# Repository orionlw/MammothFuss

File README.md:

Mammoth Fuzz
Fuzz pedal schematic using EagleCAD

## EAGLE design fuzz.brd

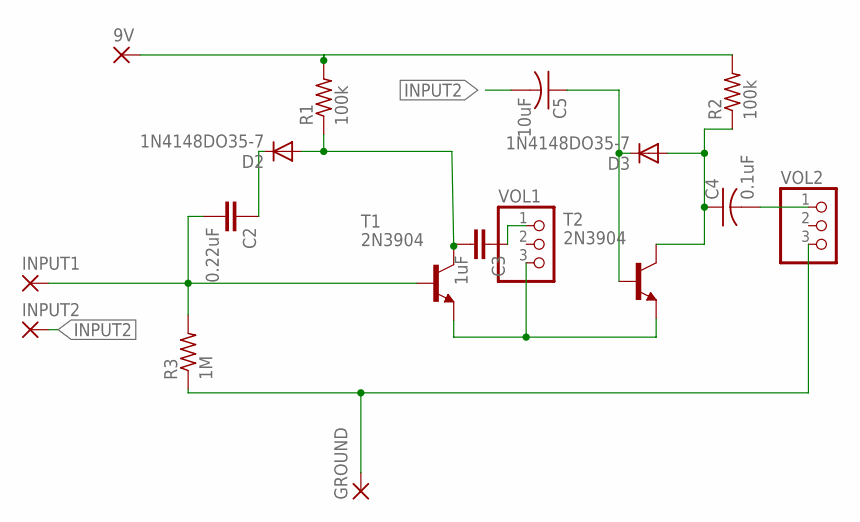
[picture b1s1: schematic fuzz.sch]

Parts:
9V: 2,15/1,0
C2: 0.22uF; C025-025X050
C3: 1uF; C025-025X050
C4: 0.1uF; C025-025X050
C5: 10uF; C025-025X050
D2, D3: 1N4148DO35-7; DO35-7
GROUND: 2,15/1,0
INPUT1, INPUT2: 2,15/1,0
R1, R2: 100k; 0207/10
R3: 1M; 0207/10
T1, T2: 2N3904; TO92
VOL1, VOL2: PINHD-1X3; 1X03

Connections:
INPUT2: C5.2, INPUT2.1
unnamed: C3.1, VOL1.1
unnamed: C2.2, INPUT1.1, R3.2, T1.2 (B)
unnamed: C3.2, D2.A, R1.1, T1.1 (C)
unnamed: C5.1, D3.C, T2.2 (B)
unnamed: C4.1, D3.A, R2.1, T2.1 (C)
unnamed: 9V.1, R1.2, R2.2
unnamed: C4.2, VOL2.1
unnamed: T1.3 (E), T2.3 (E), VOL1.3
unnamed: GROUND.1, R3.1, VOL2.3
unnamed: C2.1, D2.C

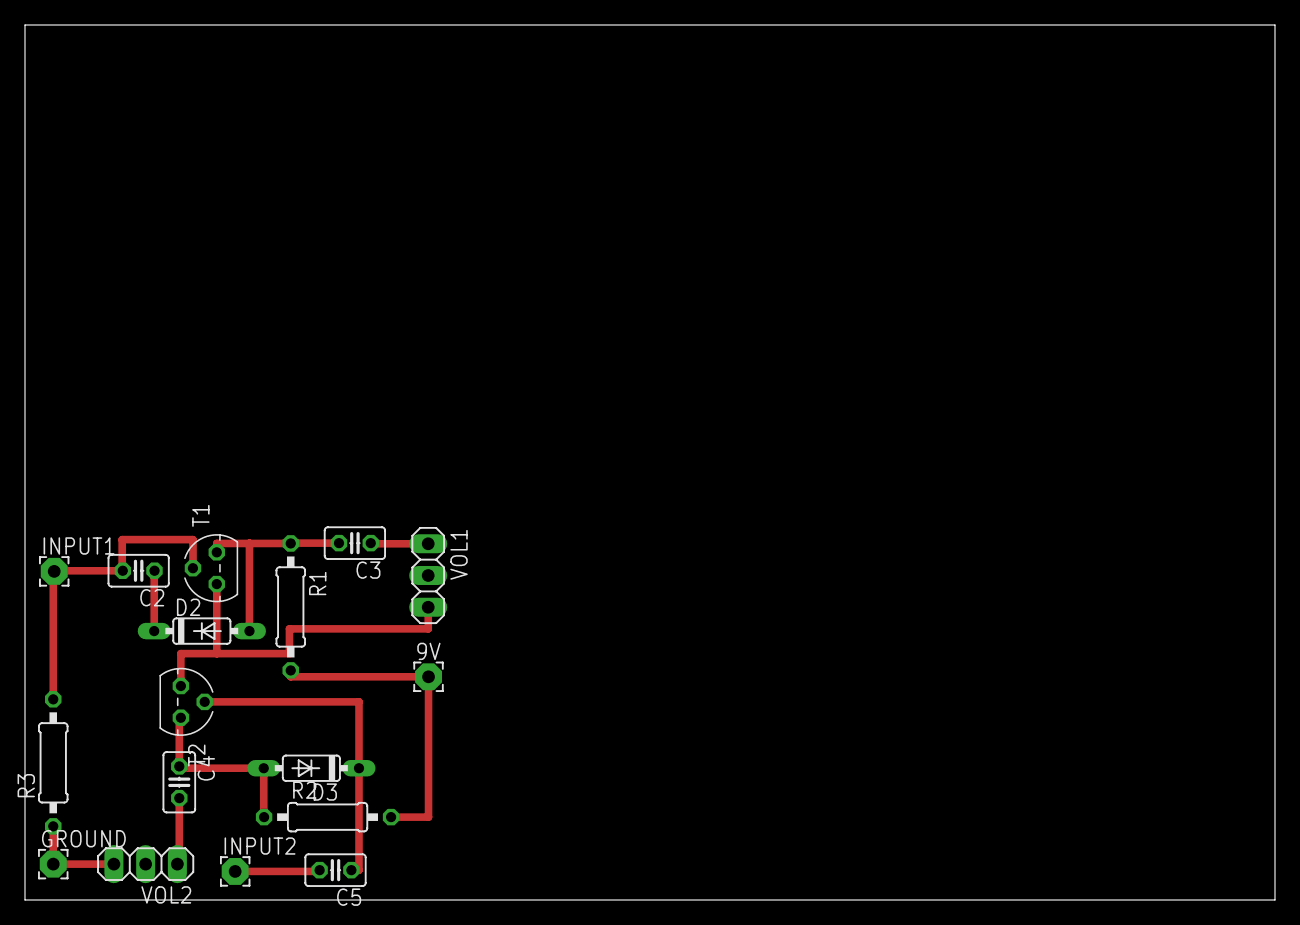
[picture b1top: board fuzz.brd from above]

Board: 2 copper layers, 100.0 x 70.0 mm, 17 parts (0 on the bottom side), 11 nets.

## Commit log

2018-01-20 1.0 Commit of Inital Schematic and Board
